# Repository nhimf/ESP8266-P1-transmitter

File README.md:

# ESP8266-P1-transmitter
This sketch written in the Arduino language makes an ESP8266 send incoming P1 smartmeter data to MQTT.

I have used this MQTT library for pubsubclient:
https://github.com/Imroy/pubsubclient

Also added in this script is an insert into an influxdb using it's UDP interface.

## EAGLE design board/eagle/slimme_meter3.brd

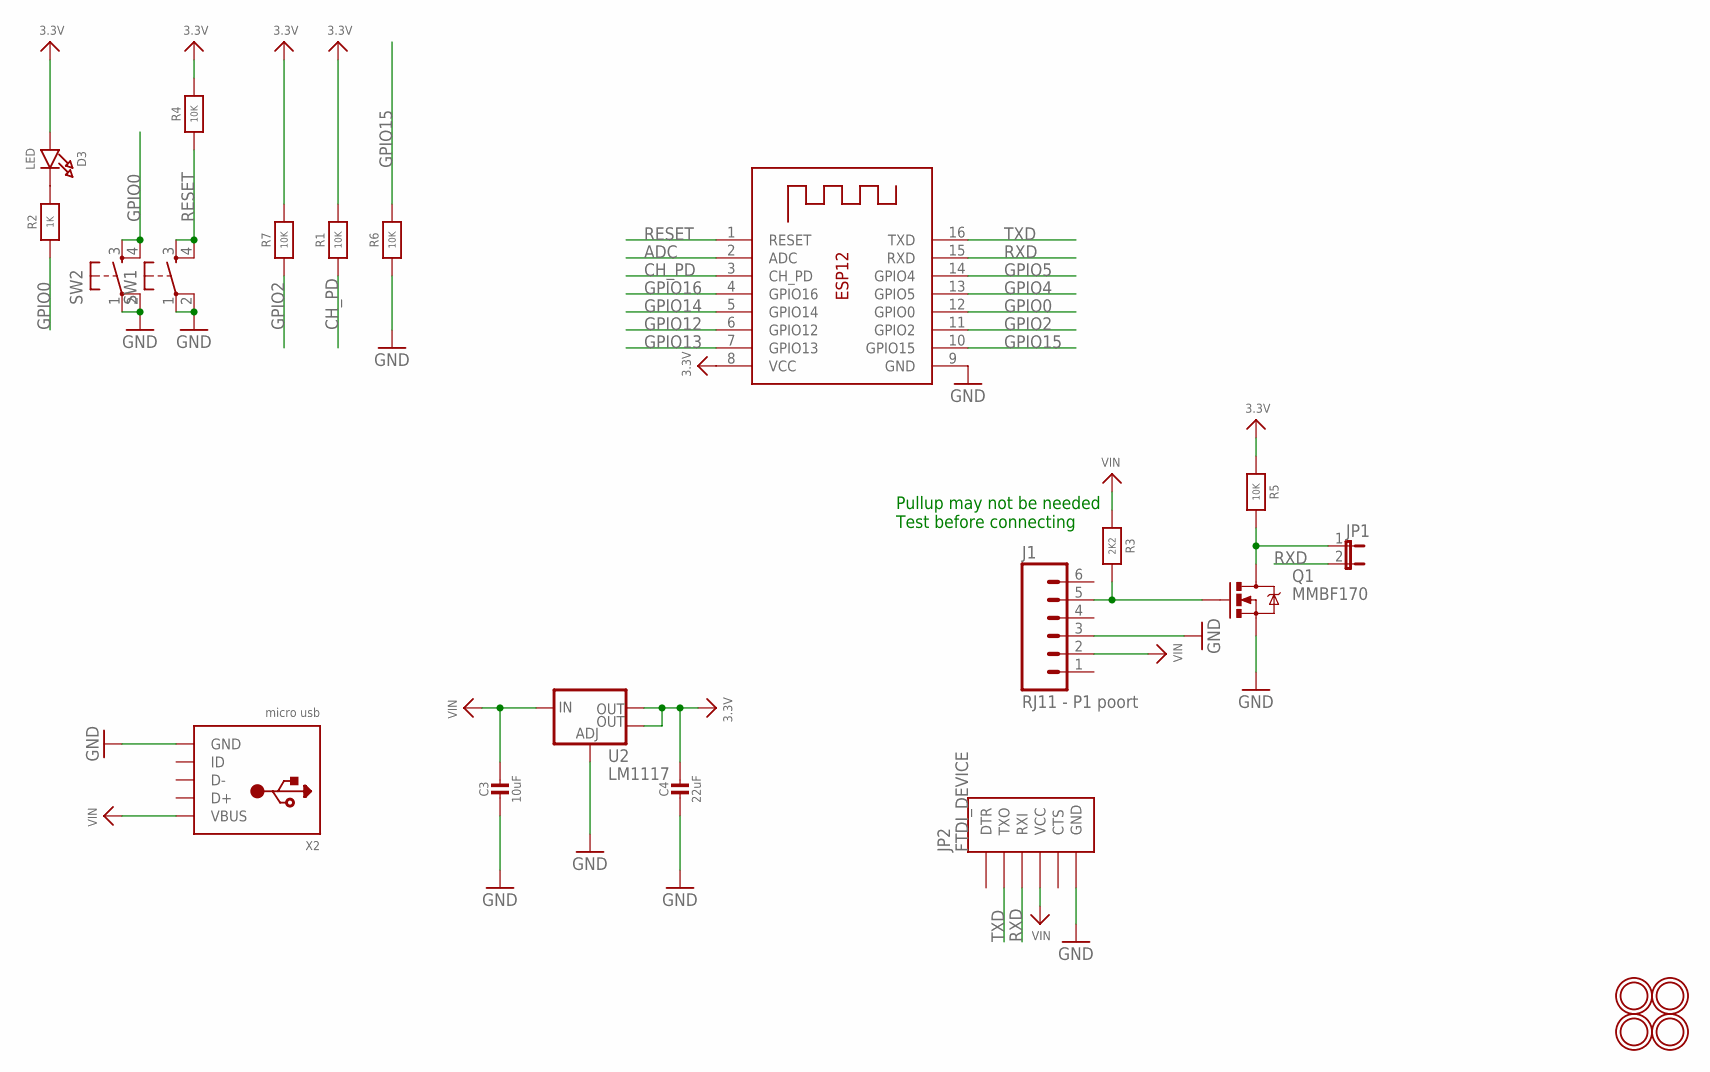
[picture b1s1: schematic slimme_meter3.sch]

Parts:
C3: 10uF; 0805-NO
C4: 22uF; 0805-NO
D3: LED; CHIPLED_0805_NOOUTLINE
J1: RJ11 - P1 poort; RJ11-6
JP1: JUMPER-2PTH; 1X02
JP2: FTDI_DEVICE; FTDI_DEVICE_SIDE
Q1: MMBF170; SOT323
R1, R4, R5, R6, R7: 10K; 0805-NO
R2: 1K; 0805-NO
R3: 2K2; 0805-NO
SW1, SW2: TACTILE-SWITCH-PTH; TAC-SWITCH-PTH
U2: LM1117; SOT223
U$15, U$16, U$17, U$18: MOUNTINGHOLE2.5; MOUNTINGHOLE_2.5_PLATED
X1: ESP-12
X2: micro usb; 4UCONN_20329

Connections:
3.3V: C4.1, D3.A, R1.2, R4.2, R5.1, R7.2, U2.2 (OUT), U2.4 (OUT), X1.8 (VCC)
ADC: X1.2 (ADC)
CH_PD: R1.1, X1.3 (CH_PD)
GND: C3.2, C4.2, J1.3, JP2.P$6 (GND), Q1.2 (S), R6.1, SW1.1, SW1.2, SW2.1, SW2.2, U2.1 (ADJ), X1.9 (GND), X2.BASE@1 (GND), X2.BASE@2 (GND), X2.GND, X2.SPRT@1 (GND), X2.SPRT@2 (GND), X2.SPRT@3 (GND), X2.SPRT@4 (GND)
GPIO0: R2.1, SW2.3, SW2.4, X1.12 (GPIO0)
GPIO2: R7.1, X1.11 (GPIO2)
GPIO4: X1.13 (GPIO5)
GPIO5: X1.14 (GPIO4)
GPIO12: X1.6 (GPIO12)
GPIO13: X1.7 (GPIO13)
GPIO14: X1.5 (GPIO14)
GPIO15: R6.2, X1.10 (GPIO15)
GPIO16: X1.4 (GPIO16)
unnamed: D3.C, R2.2
unnamed: JP1.1, Q1.3 (D), R5.2
unnamed: J1.5, Q1.1 (G), R3.2
RESET: R4.1, SW1.3, SW1.4, X1.1 (RESET)
RXD: JP1.2, JP2.P$3 (RXI), X1.15 (RXD)
TXD: JP2.P$2 (TXO), X1.16 (TXD)
VIN: C3.1, J1.2, JP2.P$4 (VCC), R3.1, U2.3 (IN), X2.VBUS

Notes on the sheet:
Pullup may not be needed Test before connecting

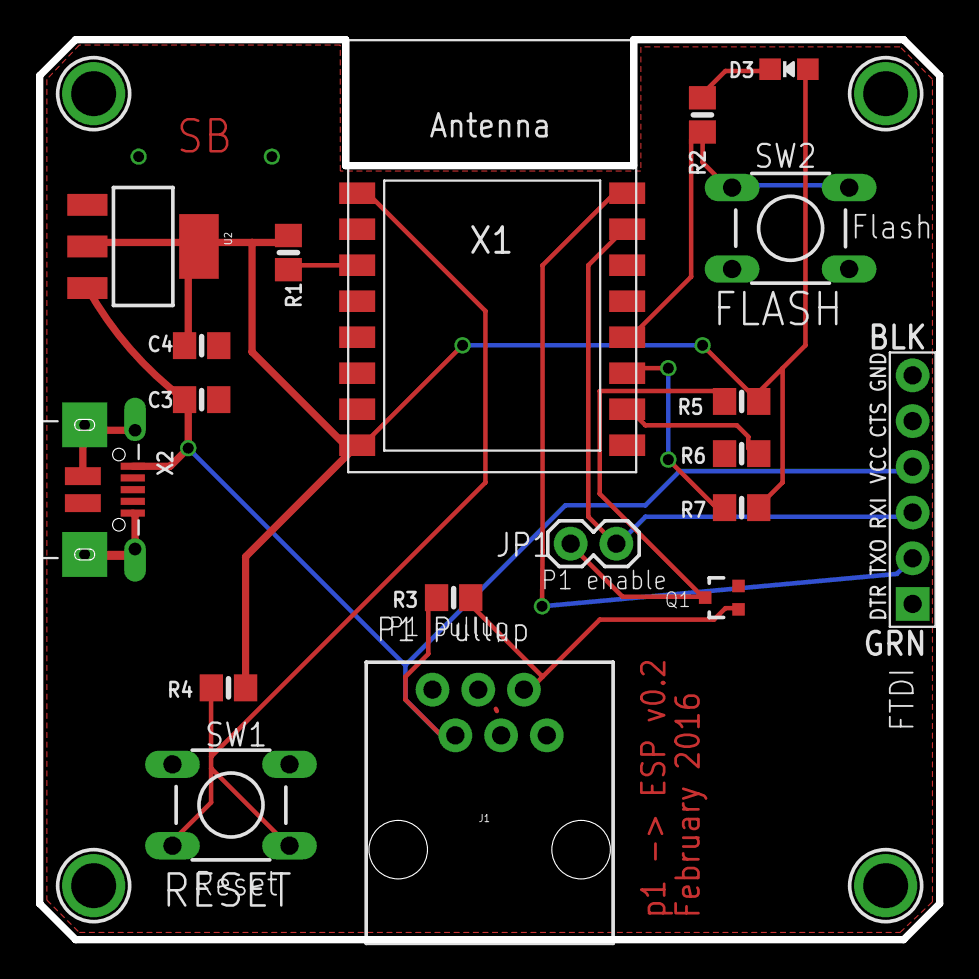
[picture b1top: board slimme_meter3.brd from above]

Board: 2 copper layers, 50.0 x 50.0 mm, 23 parts (0 on the bottom side), 13 nets.

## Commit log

2016-01-23 first working script without posting to the cloud
2016-01-23 added .gitignore for config
2016-01-23 one time add config.h
2016-01-23 added correct .gitignore
2016-01-24 remove some more stuff en rearranged code
2016-01-24 did some more cleaning and rearranging
2016-01-31 we have influx now
2016-01-31 changed comment on influxdb ip and port
2016-04-09 merged influxdb delivery
2016-04-09 added board
2017-10-20 - Construct a full telegram before parsing - Parsing still sucks so must be revised.

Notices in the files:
parts and their libraries:
microbuilder: This work is placed in the public domain, and may be freely used for commercial and non-commercial work with the following conditions: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
SparkFun-Connectors: Licensing: Creative Commons ShareAlike 4.0 International - https://creativecommons.org/licenses/by-sa/4.0
